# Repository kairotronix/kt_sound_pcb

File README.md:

# kt_sound_pcb

This is the schematic and PCB design files for interfacing with the DE10-Nano development kit for the KT Sound FPGA synthesizer design.

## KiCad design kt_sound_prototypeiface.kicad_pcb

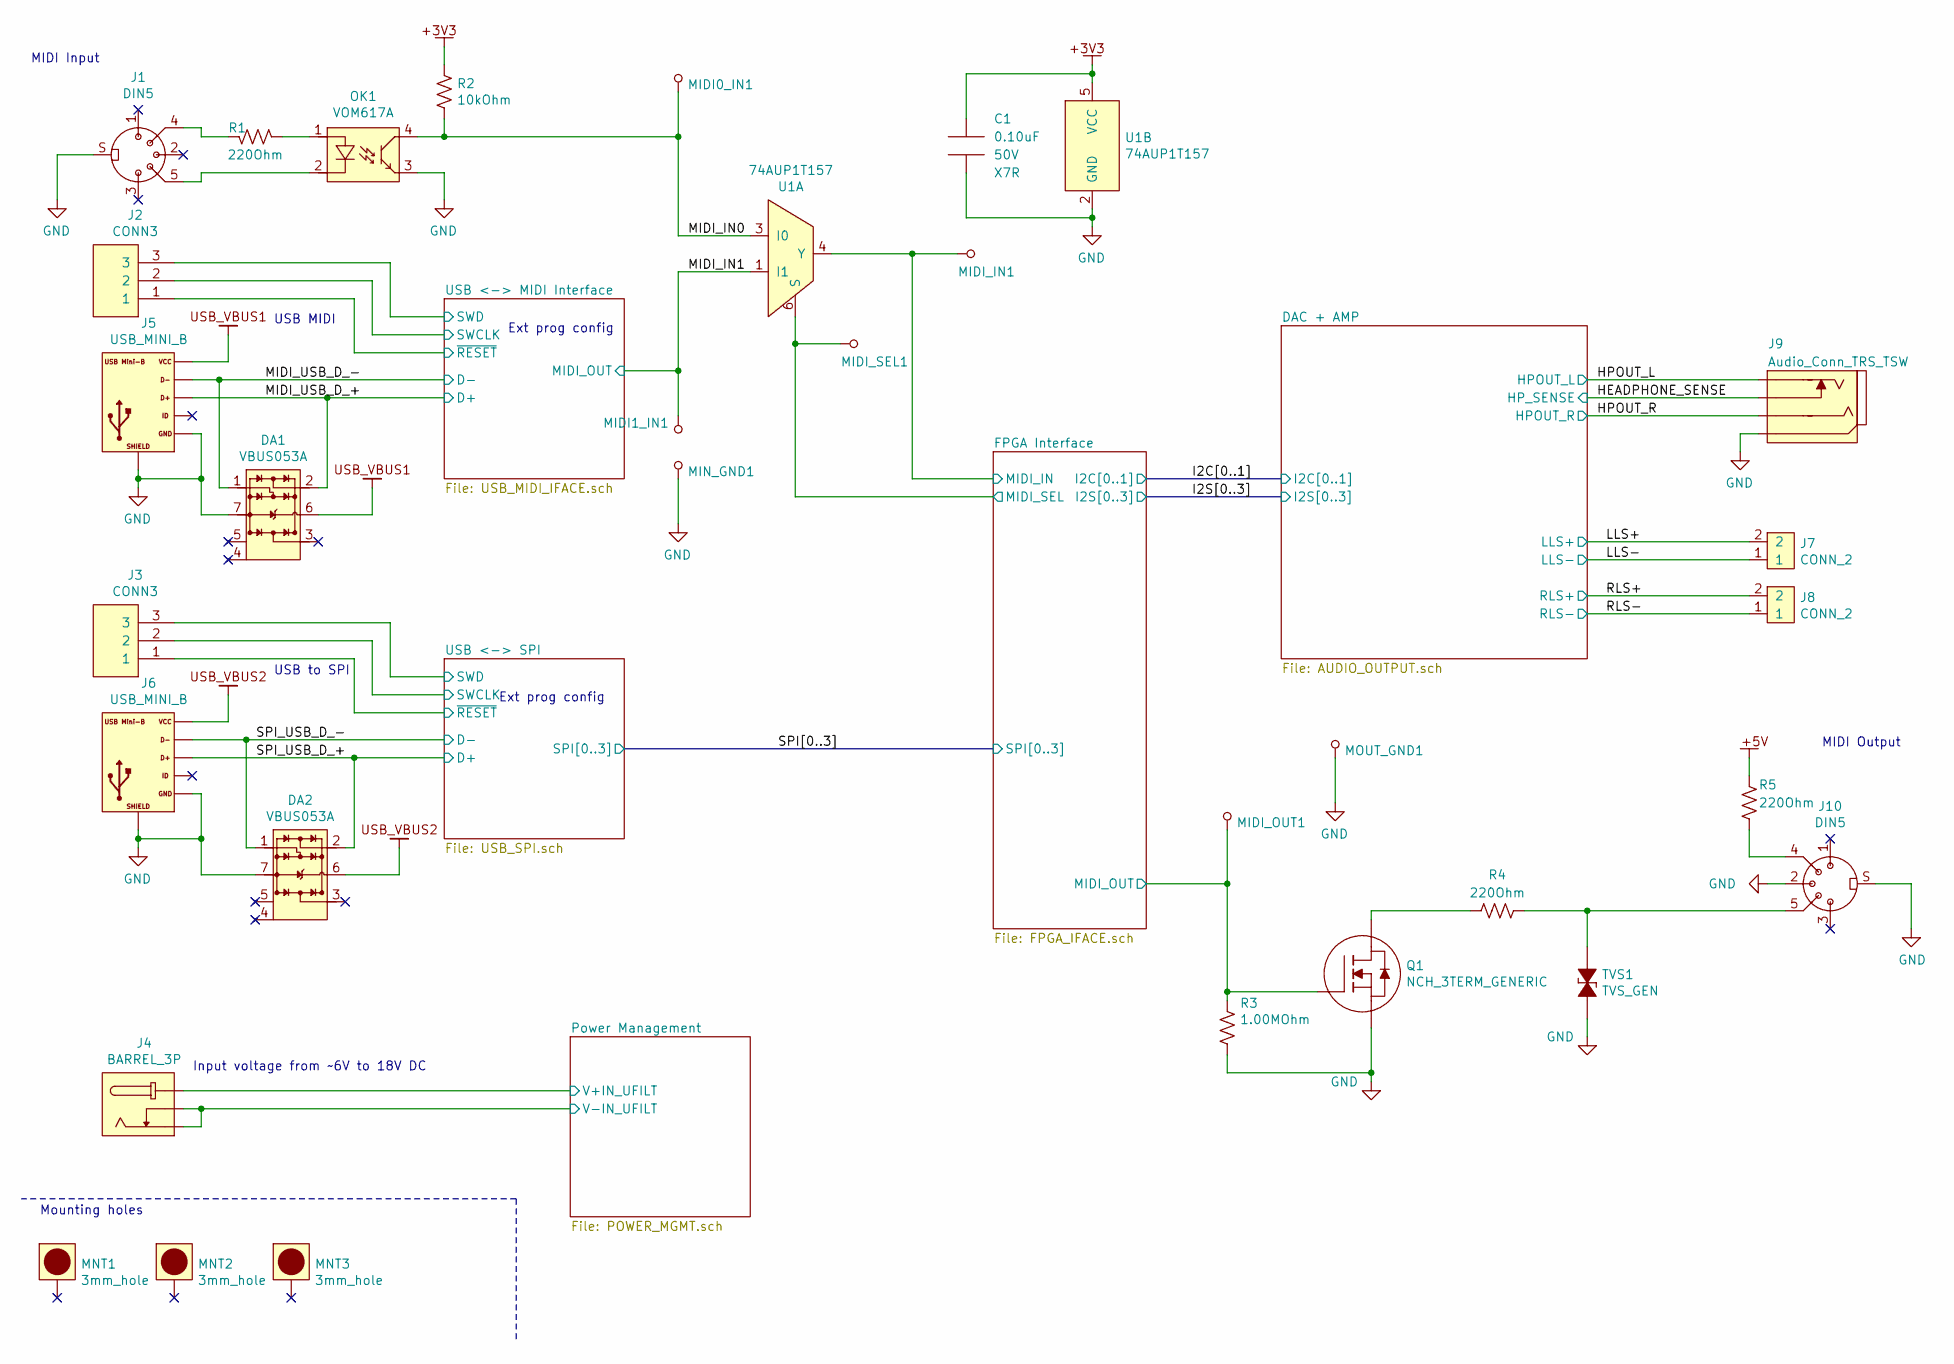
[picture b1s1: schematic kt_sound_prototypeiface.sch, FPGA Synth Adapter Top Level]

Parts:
C1: 0.10uF; CAP_0603; Voltage 50V; Tolerance XX %
DA1, DA2: VBUS053A; UFDFN-6-EP; MFG1 P/N VBUS053A
J1, J10: DIN5; DIN-5-CUI
J2, J3: CONN3; 1x03_0.1inch_vertical_header
J4: BARREL_3P; BarrelJack_CUI_PJ-102B; MFG1 P/N MFG1 P/N
J5, J6: USB_MINI_B; USB_MINIB_THT_TE_2172034-1
J7, J8: CONN_2; 1x02_0.1inch_vertical_header; MFG1 P/N MFG1 P/N
J9: Audio_Conn_TRS_TSW; Jack_3.5mm_CUI_SJ-3524-SMT; MFG1 P/N MFG1 P/N
MIDI0_IN1, MIDI1_IN1: TP_SMALL; TP_1mm; MFG P/N N/A
MIDI_IN1: TP_SMALL; TP_1mm; MFG P/N N/A
MIDI_OUT1: TP_SMALL; TP_1mm; MFG P/N N/A
MIDI_SEL1: TP_SMALL; TP_1mm; MFG P/N N/A
MIN_GND1: TP_SMALL; TP_1mm; MFG P/N N/A
MNT1, MNT2, MNT3: 3mm_hole; mnt_3mm_plated
MOUT_GND1: TP_SMALL; TP_1mm; MFG P/N N/A
OK1: VOM617A; 4-SMD_GW; MFG1 P/N VOM617A
Q1: NCH_3TERM_GENERIC; SOT23
R1: 220Ohm; RES_0603; Tolerance XX %
R2: 10kOhm; RES_0603; Tolerance XX %
R3: 1.00MOhm; RES_0603; Tolerance 10 %
R4, R5: 220Ohm; RES_0603; Tolerance 10 %
TVS1: TVS_GEN; SOD-523; Voltage - Reverse Stand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 X V; Voltage - Breakdown X V; MFG1 P/N MFG1 P/N
U1: 74AUP1T157; TSSOP-6; MFG1 P/N SN74AUP1T157

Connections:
3V3: C1.1, R2.1, U1.5 (VCC); also elsewhere on the board
5V: R5.2; also elsewhere on the board
/FPGA Interface/MIDI_IN: MIDI_IN1.1, U1.4 (Y); also elsewhere on the board
/FPGA Interface/MIDI_OUT: MIDI_OUT1.1, Q1.1 (G), R3.1; also elsewhere on the board
/FPGA Interface/MIDI_SEL: MIDI_SEL1.1, U1.6 (S); also elsewhere on the board
/HEADPHONE_SENSE: J9.10 (TS); also elsewhere on the board
/HPOUT_L: J9.2 (T); also elsewhere on the board
/HPOUT_R: J9.3 (R); also elsewhere on the board
/LLS+: J7.2; also elsewhere on the board
/LLS-: J7.1; also elsewhere on the board
/MIDI_IN0: MIDI0_IN1.1, OK1.4, R2.2, U1.3 (I0)
/MIDI_IN1: MIDI1_IN1.1, U1.1 (I1); also elsewhere on the board
/MIDI_USB_D_+: DA1.2 (I/O), J5.3; also elsewhere on the board
/MIDI_USB_D_-: DA1.1 (I/O), J5.2; also elsewhere on the board
/Power Management/V+IN_UFILT: J4.1 (BARREL); also elsewhere on the board
/RLS+: J8.2; also elsewhere on the board
/RLS-: J8.1; also elsewhere on the board
/SPI_USB_D_+: DA2.2 (I/O), J6.3; also elsewhere on the board
/SPI_USB_D_-: DA2.1 (I/O), J6.2; also elsewhere on the board
/USB <-> MIDI Interface/SWCLK: J2.2; also elsewhere on the board
/USB <-> MIDI Interface/SWD: J2.3; also elsewhere on the board
/USB <-> MIDI Interface/~RESET: J2.1; also elsewhere on the board
/USB <-> SPI/SWCLK: J3.2; also elsewhere on the board
/USB <-> SPI/SWD: J3.3; also elsewhere on the board
/USB <-> SPI/~RESET: J3.1; also elsewhere on the board
GND: C1.2, DA1.7 (GND), DA2.7 (GND), J1.S, J4.2 (SHIELD), J4.3 (CONTACT), J5.5, J5.SHIELD, J6.5, J6.SHIELD, J9.1 (S), J10.2, J10.S, MIN_GND1.1, MOUT_GND1.1, OK1.3, Q1.2 (S), R3.2, TVS1.2, U1.2 (GND); also elsewhere on the board
unnamed: J1.4, R1.1
unnamed: J1.5, OK1.2
unnamed: J10.4, R5.1
unnamed: J10.5, R4.1, TVS1.1
unnamed: OK1.1, R1.2
unnamed: Q1.3 (D), R4.2
USB_VBUS1: DA1.6 (V-), J5.1; also elsewhere on the board
USB_VBUS2: DA2.6 (V-), J6.1; also elsewhere on the board

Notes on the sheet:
USB to SPI
USB MIDI
MIDI Output
MIDI Input
Ext prog config
Input voltage from ~~6V to 18V DC
Mounting holes

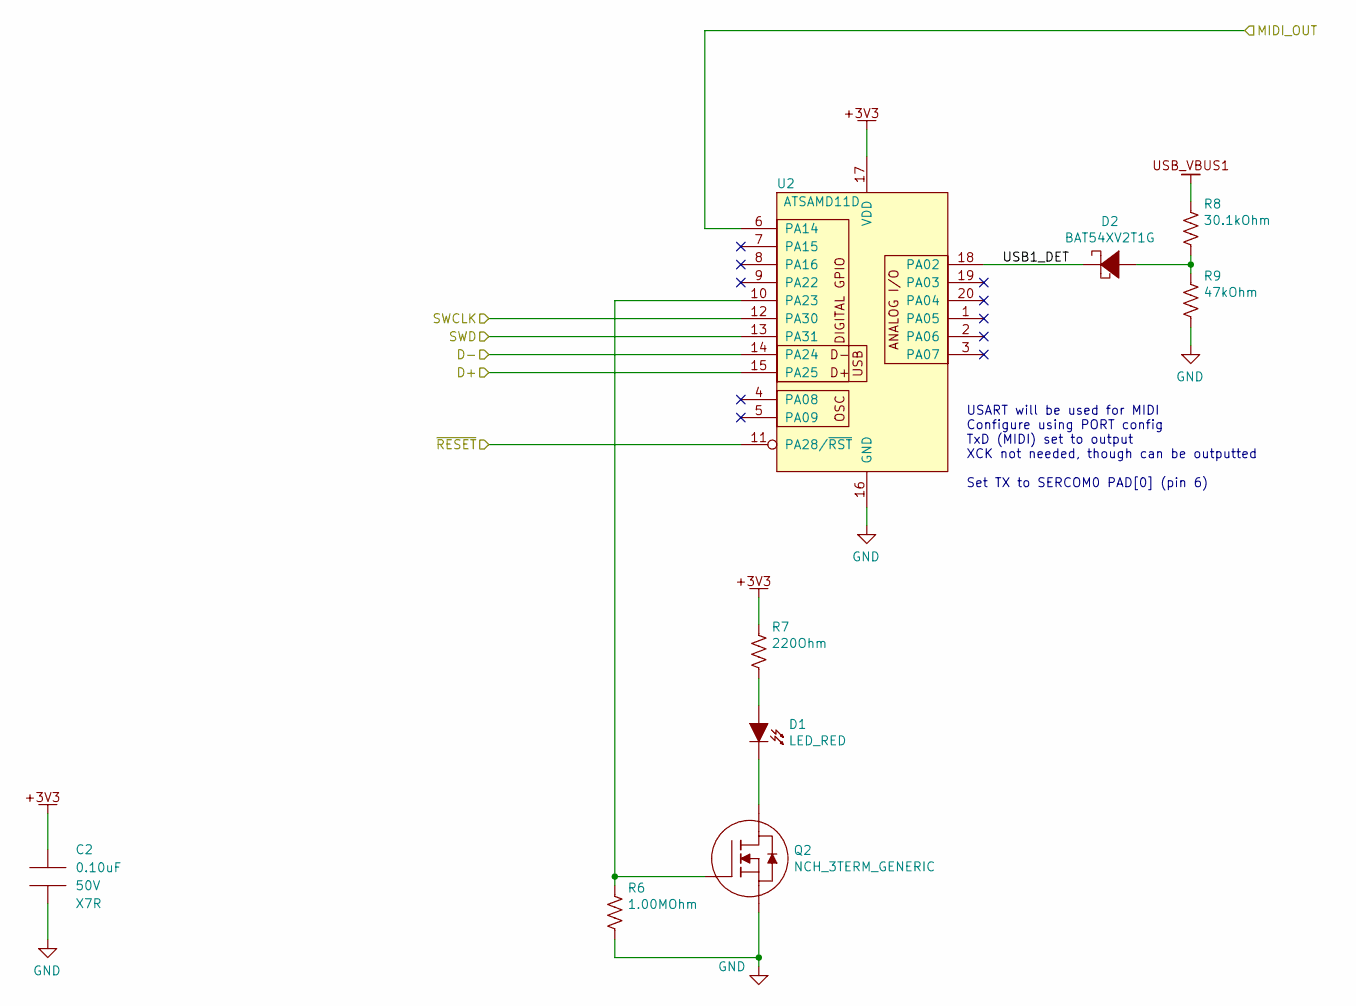
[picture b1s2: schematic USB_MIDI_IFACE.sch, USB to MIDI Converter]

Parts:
C2: 0.10uF; CAP_0603; Voltage 50V; Tolerance XX %
D1: LED_RED; LED_0805
D2: BAT54XV2T1G; SOD-523
Q2: NCH_3TERM_GENERIC; SOT23
R6: 1.00MOhm; RES_0603; Tolerance 10 %
R7: 220Ohm; RES_0603; Tolerance XX %
R8: 30.1kOhm; RES_0603; Tolerance XX %
R9: 47kOhm; RES_0603; Tolerance XX %
U2: ATSAMD11D; SOIC-20; MFG1 P/N ATSAMD11D14A-SSUT

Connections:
3V3: C2.1, R7.1, U2.17 (VDD); also elsewhere on the board
/MIDI_IN1: U2.6 (PA14); also elsewhere on the board
/MIDI_USB_D_+: U2.15 (PA25); also elsewhere on the board
/MIDI_USB_D_-: U2.14 (PA24); also elsewhere on the board
/USB <-> MIDI Interface/SWCLK: U2.12 (PA30); also elsewhere on the board
/USB <-> MIDI Interface/SWD: U2.13 (PA31); also elsewhere on the board
/USB <-> MIDI Interface/USB1_DET: D2.2, U2.18 (PA02)
/USB <-> MIDI Interface/~RESET: U2.11 (PA28/~RST); also elsewhere on the board
GND: C2.2, Q2.2 (S), R6.2, R9.2, U2.16 (GND); also elsewhere on the board
unnamed: D1.1, R7.2
unnamed: D1.2, Q2.3 (D)
unnamed: D2.1, R8.2, R9.1
unnamed: Q2.1 (G), R6.1, U2.10 (PA23)
USB_VBUS1: R8.1; also elsewhere on the board

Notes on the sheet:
USART will be used for MIDI Configure using PORT config TxD (MIDI) set to output XCK not needed, though can be outputted Set TX to SERCOM0 PAD[0] (pin 6)

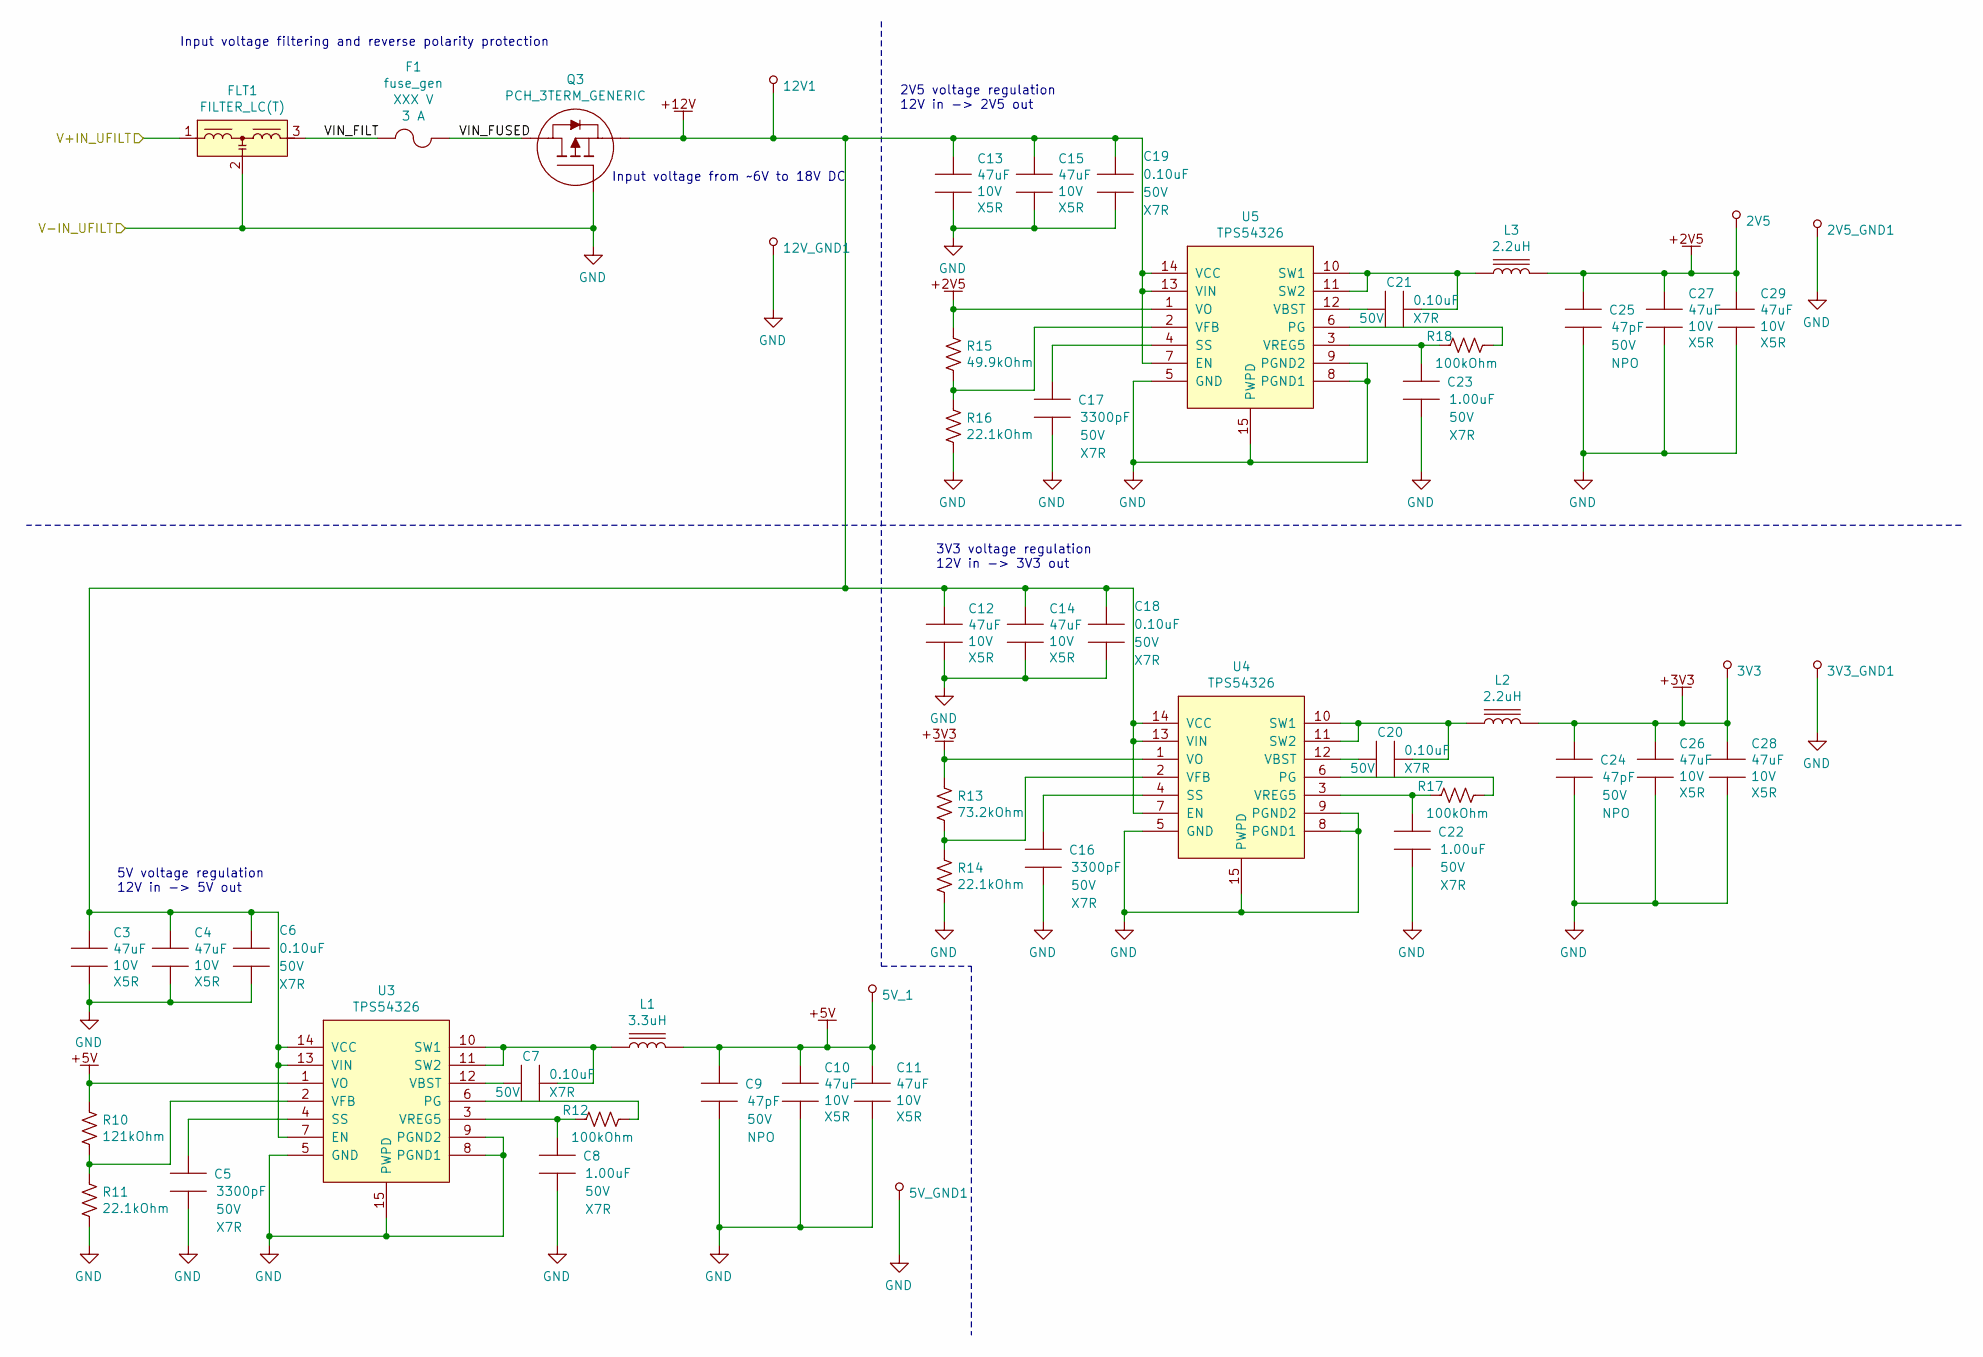
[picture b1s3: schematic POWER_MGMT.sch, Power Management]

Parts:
2V5, 2V5_GND1, 3V3, 3V3_GND1, 5V_1, 5V_GND1, 12V1, 12V_GND1: TP_SMALL; TP_1mm; MFG P/N N/A
C3, C4, C10, C11, C12, C13, C14, C15, C26, C27, C28, C29: 47uF; CAP_0805; Voltage 10V; Tolerance XX %
C5, C16, C17: 3300pF; CAP_0603; Voltage 50V; Tolerance XX %
C6, C7, C18, C19, C20, C21: 0.10uF; CAP_0603; Voltage 50V; Tolerance XX %
C8, C22, C23: 1.00uF; CAP_0603; Voltage 50V; Tolerance XX %
C9, C24, C25: 47pF; CAP_0603; Voltage 50V; Tolerance XX %
F1: fuse_gen; RES_0603; Voltage XXX V; MFG1 P/N MFG1 P/N
FLT1: FILTER_LC(T); FIL_NFE31PT222Z1E9L
L1: 3.3uH; L_Radial_THT_5mm; Voltage X V; MFG1 P/N MFG1 P/N
L2, L3: 2.2uH; L_Radial_THT_5mm; Voltage X V; MFG1 P/N MFG1 P/N
Q3: PCH_3TERM_GENERIC; SOT23
R10: 121kOhm; RES_0603; Tolerance XX %
R11, R14, R16: 22.1kOhm; RES_0603; Tolerance XX %
R12, R17, R18: 100kOhm; RES_0603; Tolerance XX %
R13: 73.2kOhm; RES_0603; Tolerance XX %
R15: 49.9kOhm; RES_0603; Tolerance XX %
U3, U4, U5: TPS54326; HTSSOP-14-EP; MFG1 P/N TPS54326

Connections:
2V5: 2V5.1, C25.1, C27.1, C29.1, L3.2, R15.1, U5.1 (VO); also elsewhere on the board
3V3: 3V3.1, C24.1, C26.1, C28.1, L2.2, R13.1, U4.1 (VO); also elsewhere on the board
5V: 5V_1.1, C9.1, C10.1, C11.1, L1.2, R10.1, U3.1 (VO); also elsewhere on the board
12V: 12V1.1, C3.1, C4.1, C6.1, C12.1, C13.1, C14.1, C15.1, C18.1, C19.1, Q3.2 (S), U3.7 (EN), U3.13 (VIN), U3.14 (VCC), U4.7 (EN), U4.13 (VIN), U4.14 (VCC), U5.7 (EN), U5.13 (VIN), U5.14 (VCC)
/Power Management/V+IN_UFILT: FLT1.1 (Input); also elsewhere on the board
/Power Management/VIN_FILT: F1.1, FLT1.3 (Output)
/Power Management/VIN_FUSED: F1.2, Q3.3 (D)
GND: 2V5_GND1.1, 3V3_GND1.1, 5V_GND1.1, 12V_GND1.1, C3.2, C4.2, C5.2, C6.2, C8.2, C9.2, C10.2, C11.2, C12.2, C13.2, C14.2, C15.2, C16.2, C17.2, C18.2, C19.2, C22.2, C23.2, C24.2, C25.2, C26.2, C27.2, C28.2, C29.2, FLT1.2 (GND), Q3.1 (G), R11.2, R14.2, R16.2, U3.5 (GND), U3.8 (PGND1), U3.9 (PGND2), U3.15 (PWPD), U4.5 (GND), U4.8 (PGND1), U4.9 (PGND2), U4.15 (PWPD), U5.5 (GND), U5.8 (PGND1), U5.9 (PGND2), U5.15 (PWPD); also elsewhere on the board
unnamed: C5.1, U3.4 (SS)
unnamed: C7.1, U3.12 (VBST)
unnamed: C7.2, L1.1, U3.10 (SW1), U3.11 (SW2)
unnamed: C8.1, R12.1, U3.3 (VREG5)
unnamed: C16.1, U4.4 (SS)
unnamed: C17.1, U5.4 (SS)
unnamed: C20.1, U4.12 (VBST)
unnamed: C20.2, L2.1, U4.10 (SW1), U4.11 (SW2)
unnamed: C21.1, U5.12 (VBST)
unnamed: C21.2, L3.1, U5.10 (SW1), U5.11 (SW2)
unnamed: C22.1, R17.1, U4.3 (VREG5)
unnamed: C23.1, R18.1, U5.3 (VREG5)
unnamed: R10.2, R11.1, U3.2 (VFB)
unnamed: R12.2, U3.6 (PG)
unnamed: R13.2, R14.1, U4.2 (VFB)
unnamed: R15.2, R16.1, U5.2 (VFB)
unnamed: R17.2, U4.6 (PG)
unnamed: R18.2, U5.6 (PG)

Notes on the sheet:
2V5 voltage regulation 12V in -> 2V5 out
3V3 voltage regulation 12V in -> 3V3 out
5V voltage regulation 12V in -> 5V out
Input voltage filtering and reverse polarity protection
Input voltage from ~~6V to 18V DC

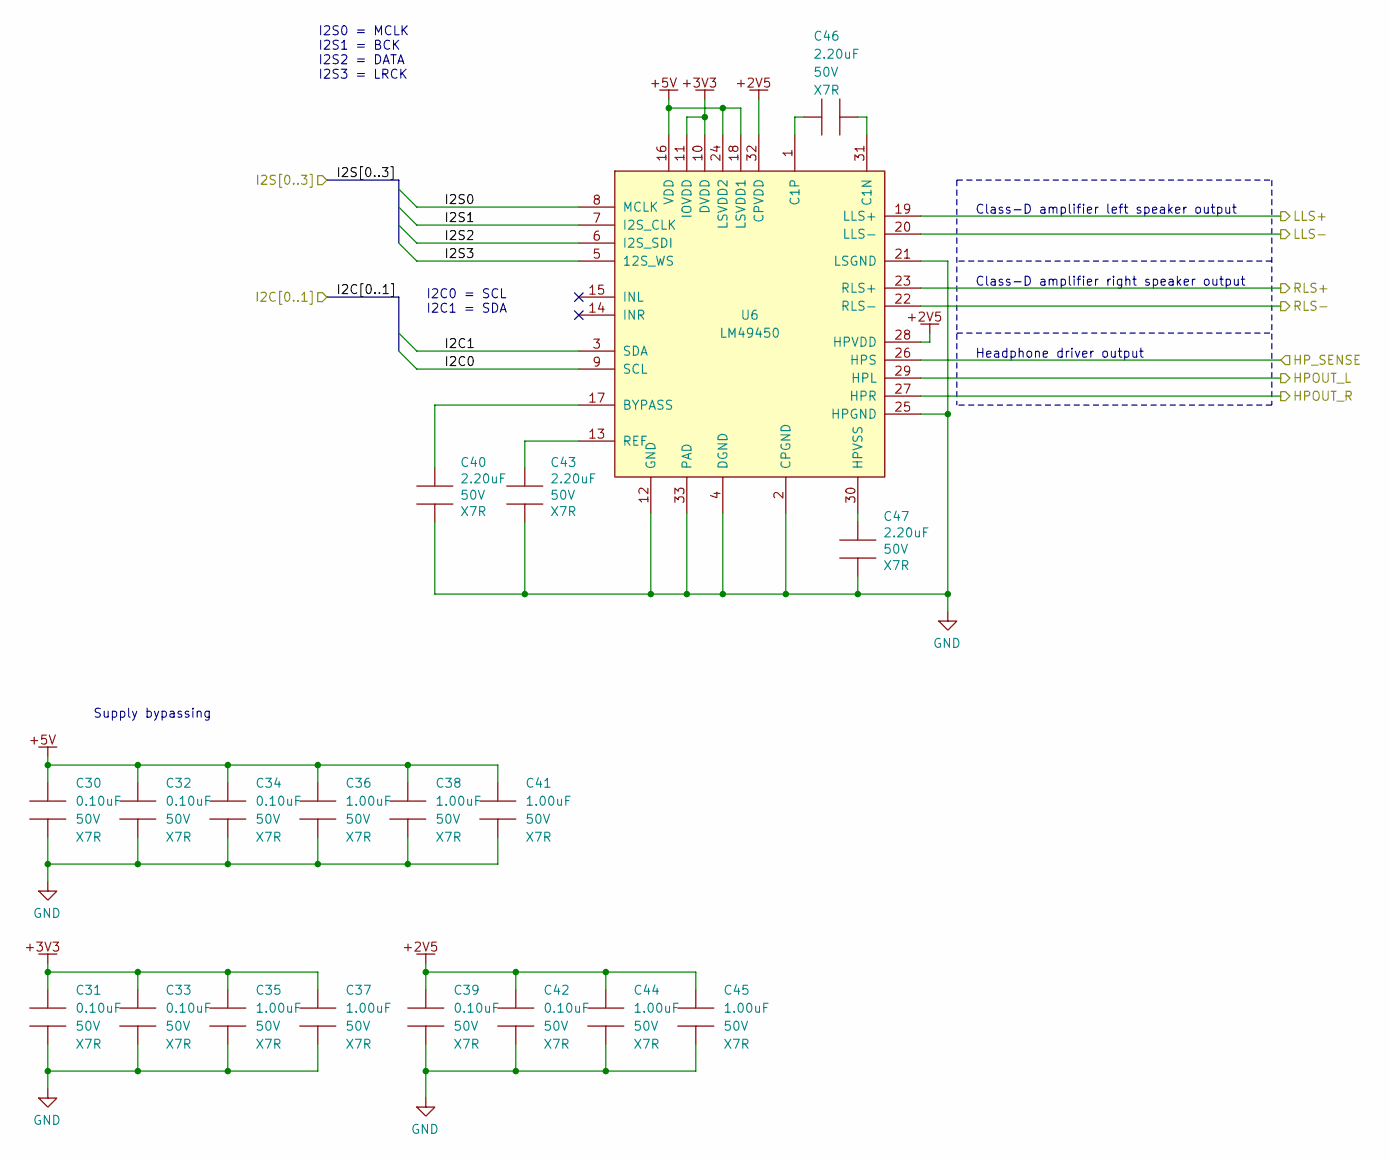
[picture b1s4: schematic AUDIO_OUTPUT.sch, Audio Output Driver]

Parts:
C30, C31, C32, C33, C34, C39, C42: 0.10uF; CAP_0603; Voltage 50V; Tolerance XX %
C35, C36, C37, C38, C41, C44, C45: 1.00uF; CAP_0603; Voltage 50V; Tolerance XX %
C40, C43, C46, C47: 2.20uF; CAP_0603; Voltage 50V; Tolerance XX %
U6: LM49450; WQFN-32; MFG1 P/N LM49450

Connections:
2V5: C39.1, C42.1, C44.1, C45.1, U6.28 (HPVDD), U6.32 (CPVDD); also elsewhere on the board
3V3: C31.1, C33.1, C35.1, C37.1, U6.10 (DVDD), U6.11 (IOVDD); also elsewhere on the board
5V: C30.1, C32.1, C34.1, C36.1, C38.1, C41.1, U6.16 (VDD), U6.18 (LSVDD1), U6.24 (LSVDD2); also elsewhere on the board
/DAC + AMP/I2C0: U6.9 (SCL); also elsewhere on the board
/DAC + AMP/I2C1: U6.3 (SDA); also elsewhere on the board
/DAC + AMP/I2S0: U6.8 (MCLK); also elsewhere on the board
/DAC + AMP/I2S1: U6.7 (I2S_CLK); also elsewhere on the board
/DAC + AMP/I2S2: U6.6 (I2S_SDI); also elsewhere on the board
/DAC + AMP/I2S3: U6.5 (12S_WS); also elsewhere on the board
/HEADPHONE_SENSE: U6.26 (HPS); also elsewhere on the board
/HPOUT_L: U6.29 (HPL); also elsewhere on the board
/HPOUT_R: U6.27 (HPR); also elsewhere on the board
/LLS+: U6.19 (LLS+); also elsewhere on the board
/LLS-: U6.20 (LLS-); also elsewhere on the board
/RLS+: U6.23 (RLS+); also elsewhere on the board
/RLS-: U6.22 (RLS-); also elsewhere on the board
GND: C30.2, C31.2, C32.2, C33.2, C34.2, C35.2, C36.2, C37.2, C38.2, C39.2, C40.2, C41.2, C42.2, C43.2, C44.2, C45.2, C47.2, U6.2 (CPGND), U6.4 (DGND), U6.12 (GND), U6.21 (LSGND), U6.25 (HPGND), U6.33 (PAD); also elsewhere on the board
unnamed: C40.1, U6.17 (BYPASS)
unnamed: C43.1, U6.13 (REF)
unnamed: C46.1, U6.1 (C1P)
unnamed: C46.2, U6.31 (C1N)
unnamed: C47.1, U6.30 (HPVSS)

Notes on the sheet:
Class-D amplifier left speaker output
Class-D amplifier right speaker output
Headphone driver output
Supply bypassing
I2S0 = MCLK I2S1 = BCK I2S2 = DATA I2S3 = LRCK
I2C0 = SCL I2C1 = SDA

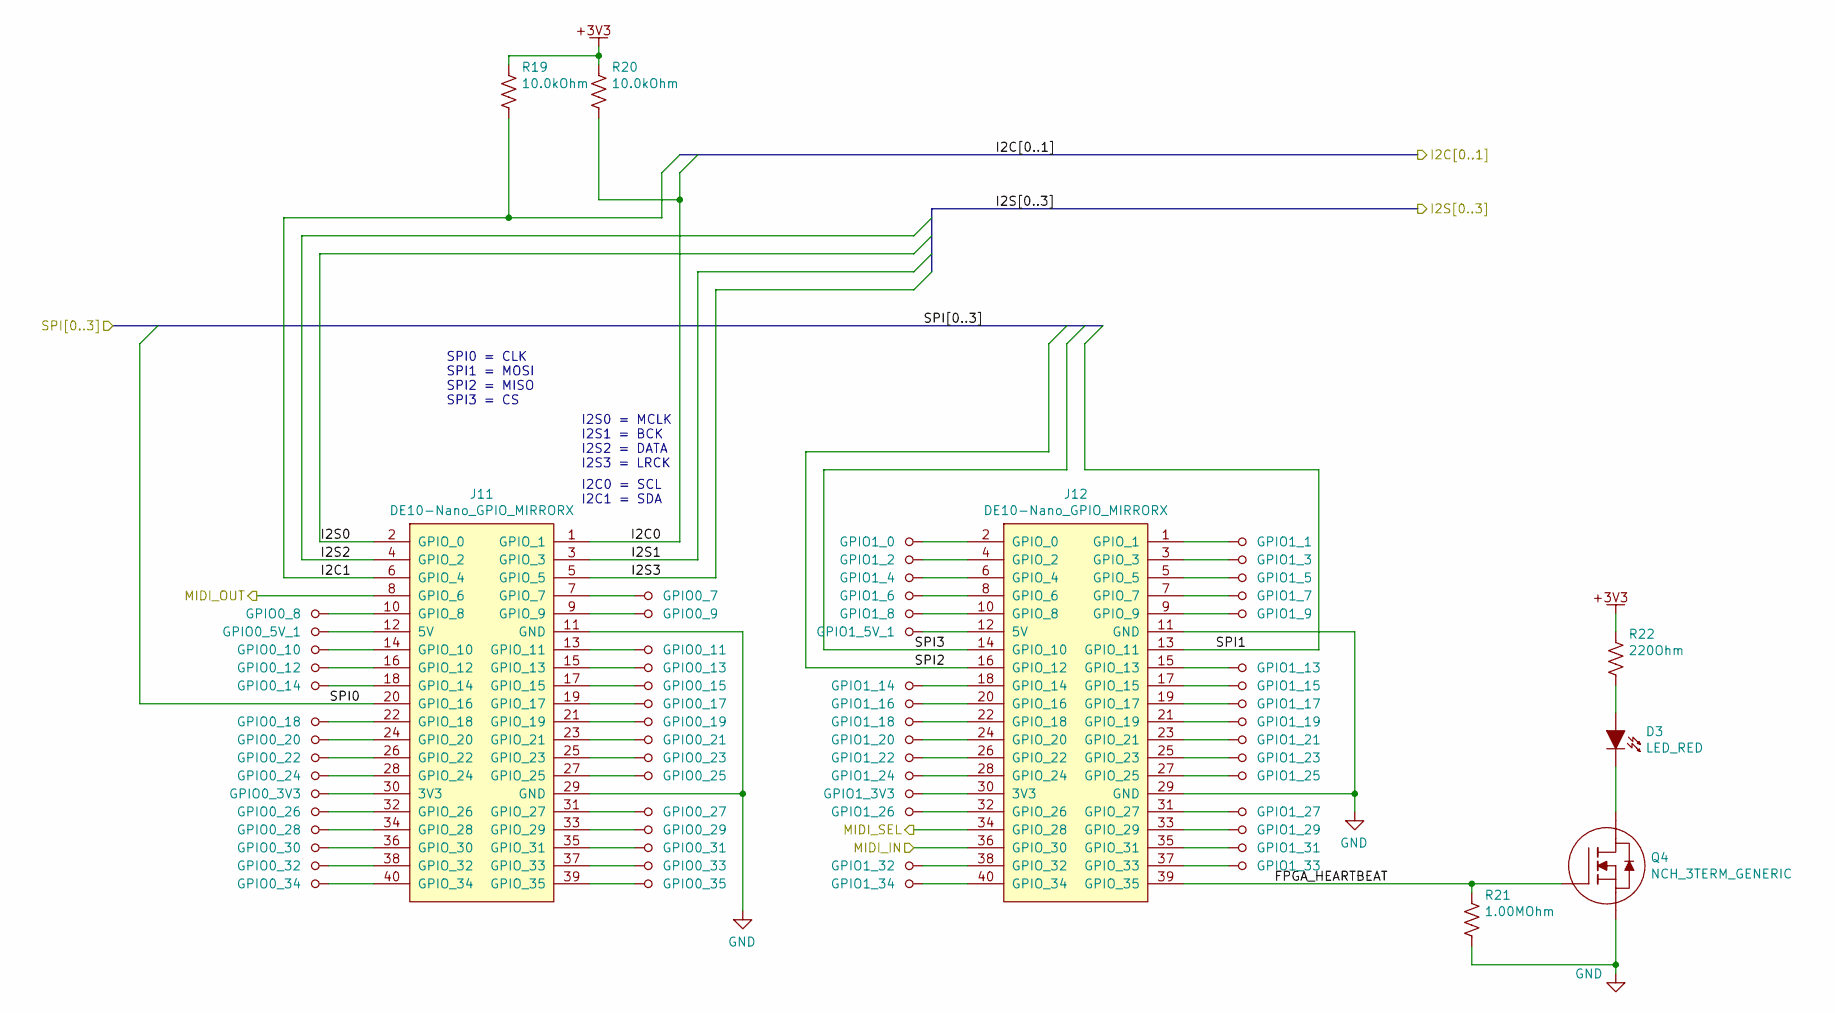
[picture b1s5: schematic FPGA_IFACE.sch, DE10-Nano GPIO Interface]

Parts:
D3: LED_RED; LED_0805
GPIO0_3V3, GPIO0_5V_1, GPIO0_7, GPIO0_8, GPIO0_9, GPIO0_10, GPIO0_11, GPIO0_12, GPIO0_13, GPIO0_14, GPIO0_15, GPIO0_17, GPIO0_18, GPIO0_19, GPIO0_20, GPIO0_21, GPIO0_22, GPIO0_23, GPIO0_24, GPIO0_25, GPIO0_26, GPIO0_27, GPIO0_28, GPIO0_29, GPIO0_30, GPIO0_31, GPIO0_32, GPIO0_33, GPIO0_34, GPIO0_35, GPIO1_0, GPIO1_1, GPIO1_2, GPIO1_3, GPIO1_3V3, GPIO1_4, GPIO1_5, GPIO1_5V_1, GPIO1_6, GPIO1_7, GPIO1_8, GPIO1_9, GPIO1_13, GPIO1_14, GPIO1_15, GPIO1_16, GPIO1_17, GPIO1_18, GPIO1_19, GPIO1_20, GPIO1_21, GPIO1_22, GPIO1_23, GPIO1_24, GPIO1_25, GPIO1_26, GPIO1_27, GPIO1_29, GPIO1_31, GPIO1_32, GPIO1_33, GPIO1_34: TP_SMALL; TP_1mm; MFG P/N N/A
J11, J12: DE10-Nano_GPIO_MIRRORX; DE10_GPIO_HEADER
Q4: NCH_3TERM_GENERIC; SOT23
R19, R20: 10.0kOhm; RES_0603; Tolerance XX %
R21: 1.00MOhm; RES_0603; Tolerance 10 %
R22: 220Ohm; RES_0603; Tolerance XX %

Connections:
3V3: R19.1, R20.1, R22.1; also elsewhere on the board
/DAC + AMP/I2C0: J11.1 (GPIO_1), R20.2; also elsewhere on the board
/DAC + AMP/I2C1: J11.6 (GPIO_4), R19.2; also elsewhere on the board
/DAC + AMP/I2S0: J11.2 (GPIO_0); also elsewhere on the board
/DAC + AMP/I2S1: J11.3 (GPIO_3); also elsewhere on the board
/DAC + AMP/I2S2: J11.4 (GPIO_2); also elsewhere on the board
/DAC + AMP/I2S3: J11.5 (GPIO_5); also elsewhere on the board
/FPGA Interface/FPGA_HEARTBEAT: J12.39 (GPIO_35), Q4.1 (G), R21.1
/FPGA Interface/MIDI_IN: J12.36 (GPIO_30); also elsewhere on the board
/FPGA Interface/MIDI_OUT: J11.8 (GPIO_6); also elsewhere on the board
/FPGA Interface/MIDI_SEL: J12.34 (GPIO_28); also elsewhere on the board
/FPGA Interface/SPI0: J11.20 (GPIO_16); also elsewhere on the board
/FPGA Interface/SPI1: J12.13 (GPIO_11); also elsewhere on the board
/FPGA Interface/SPI2: J12.16 (GPIO_12); also elsewhere on the board
/FPGA Interface/SPI3: J12.14 (GPIO_10); also elsewhere on the board
GND: J11.11 (GND), J11.29 (GND), J12.11 (GND), J12.29 (GND), Q4.2 (S), R21.2; also elsewhere on the board
unnamed: D3.1, R22.2
unnamed: D3.2, Q4.3 (D)
unnamed: GPIO0_3V3.1, J11.30 (3V3)
unnamed: GPIO0_5V_1.1, J11.12 (5V)
unnamed: GPIO0_7.1, J11.7 (GPIO_7)
unnamed: GPIO0_8.1, J11.10 (GPIO_8)
unnamed: GPIO0_9.1, J11.9 (GPIO_9)
unnamed: GPIO0_10.1, J11.14 (GPIO_10)
unnamed: GPIO0_11.1, J11.13 (GPIO_11)
unnamed: GPIO0_12.1, J11.16 (GPIO_12)
unnamed: GPIO0_13.1, J11.15 (GPIO_13)
unnamed: GPIO0_14.1, J11.18 (GPIO_14)
unnamed: GPIO0_15.1, J11.17 (GPIO_15)
unnamed: GPIO0_17.1, J11.19 (GPIO_17)
unnamed: GPIO0_18.1, J11.22 (GPIO_18)
unnamed: GPIO0_19.1, J11.21 (GPIO_19)
unnamed: GPIO0_20.1, J11.24 (GPIO_20)
unnamed: GPIO0_21.1, J11.23 (GPIO_21)
unnamed: GPIO0_22.1, J11.26 (GPIO_22)
unnamed: GPIO0_23.1, J11.25 (GPIO_23)
unnamed: GPIO0_24.1, J11.28 (GPIO_24)
unnamed: GPIO0_25.1, J11.27 (GPIO_25)
unnamed: GPIO0_26.1, J11.32 (GPIO_26)
unnamed: GPIO0_27.1, J11.31 (GPIO_27)
unnamed: GPIO0_28.1, J11.34 (GPIO_28)
unnamed: GPIO0_29.1, J11.33 (GPIO_29)
unnamed: GPIO0_30.1, J11.36 (GPIO_30)
unnamed: GPIO0_31.1, J11.35 (GPIO_31)
unnamed: GPIO0_32.1, J11.38 (GPIO_32)
unnamed: GPIO0_33.1, J11.37 (GPIO_33)
unnamed: GPIO0_34.1, J11.40 (GPIO_34)
unnamed: GPIO0_35.1, J11.39 (GPIO_35)
unnamed: GPIO1_0.1, J12.2 (GPIO_0)
unnamed: GPIO1_1.1, J12.1 (GPIO_1)
unnamed: GPIO1_2.1, J12.4 (GPIO_2)
unnamed: GPIO1_3.1, J12.3 (GPIO_3)
unnamed: GPIO1_3V3.1, J12.30 (3V3)
unnamed: GPIO1_4.1, J12.6 (GPIO_4)
unnamed: GPIO1_5.1, J12.5 (GPIO_5)
unnamed: GPIO1_5V_1.1, J12.12 (5V)
unnamed: GPIO1_6.1, J12.8 (GPIO_6)
unnamed: GPIO1_7.1, J12.7 (GPIO_7)
unnamed: GPIO1_8.1, J12.10 (GPIO_8)
unnamed: GPIO1_9.1, J12.9 (GPIO_9)
unnamed: GPIO1_13.1, J12.15 (GPIO_13)
unnamed: GPIO1_14.1, J12.18 (GPIO_14)
unnamed: GPIO1_15.1, J12.17 (GPIO_15)
unnamed: GPIO1_16.1, J12.20 (GPIO_16)
unnamed: GPIO1_17.1, J12.19 (GPIO_17)
unnamed: GPIO1_18.1, J12.22 (GPIO_18)
unnamed: GPIO1_19.1, J12.21 (GPIO_19)
unnamed: GPIO1_20.1, J12.24 (GPIO_20)
unnamed: GPIO1_21.1, J12.23 (GPIO_21)
unnamed: GPIO1_22.1, J12.26 (GPIO_22)
unnamed: GPIO1_23.1, J12.25 (GPIO_23)
unnamed: GPIO1_24.1, J12.28 (GPIO_24)
unnamed: GPIO1_25.1, J12.27 (GPIO_25)
unnamed: GPIO1_26.1, J12.32 (GPIO_26)
unnamed: GPIO1_27.1, J12.31 (GPIO_27)
unnamed: GPIO1_29.1, J12.33 (GPIO_29)
unnamed: GPIO1_31.1, J12.35 (GPIO_31)
unnamed: GPIO1_32.1, J12.38 (GPIO_32)
unnamed: GPIO1_33.1, J12.37 (GPIO_33)
unnamed: GPIO1_34.1, J12.40 (GPIO_34)

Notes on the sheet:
I2S0 = MCLK I2S1 = BCK I2S2 = DATA I2S3 = LRCK
I2C0 = SCL I2C1 = SDA
SPI0 = CLK SPI1 = MOSI SPI2 = MISO SPI3 = CS

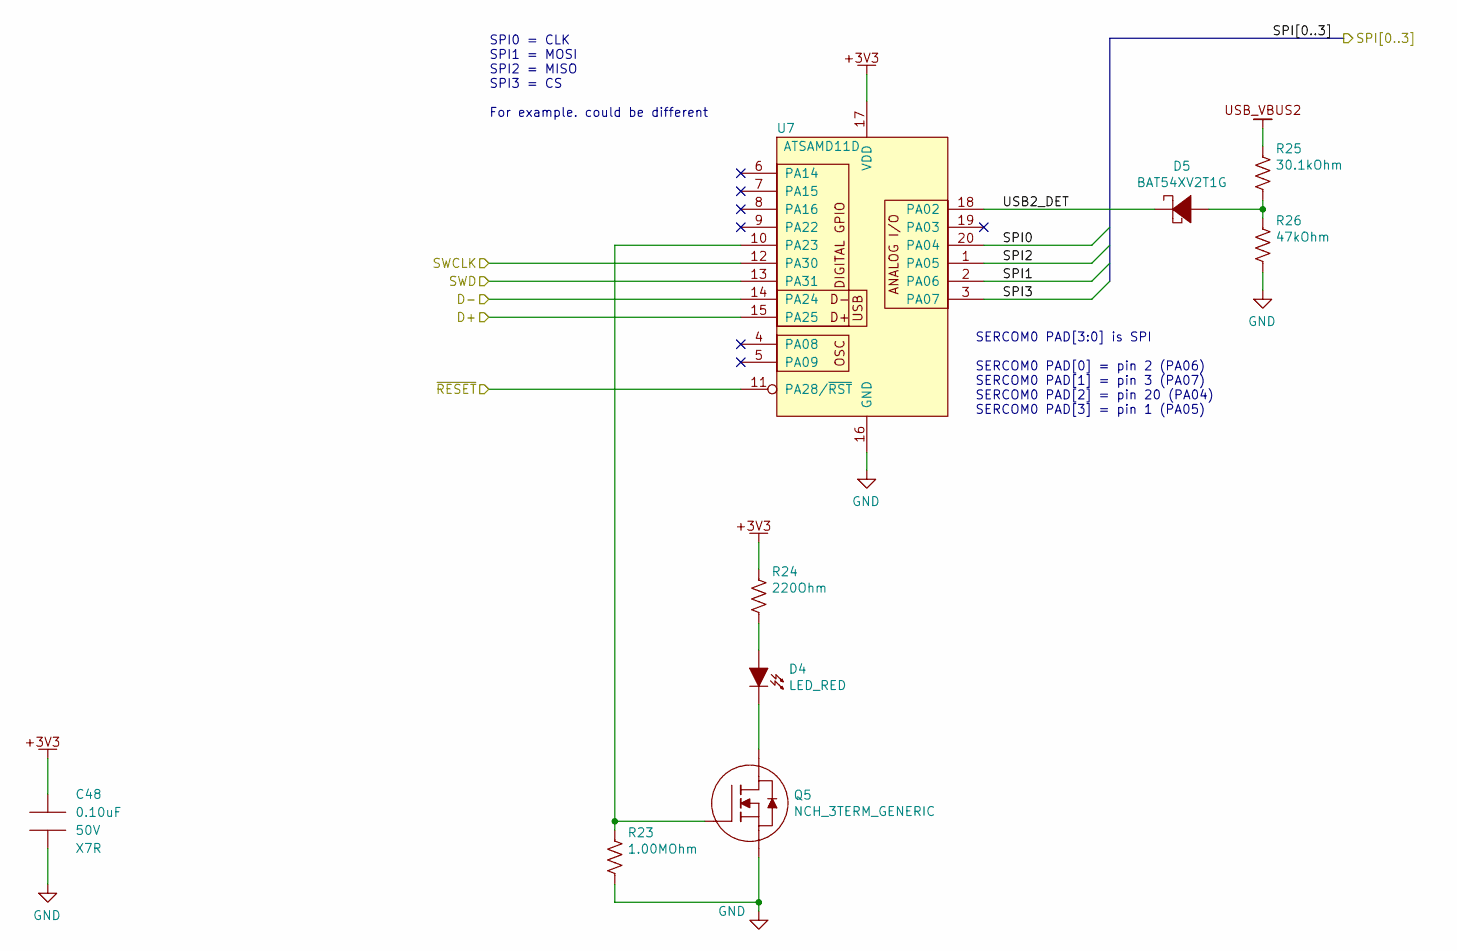
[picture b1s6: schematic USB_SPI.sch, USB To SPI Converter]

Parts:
C48: 0.10uF; CAP_0603; Voltage 50V; Tolerance XX %
D4: LED_RED; LED_0805
D5: BAT54XV2T1G; SOD-523
Q5: NCH_3TERM_GENERIC; SOT23
R23: 1.00MOhm; RES_0603; Tolerance 10 %
R24: 220Ohm; RES_0603; Tolerance XX %
R25: 30.1kOhm; RES_0603; Tolerance XX %
R26: 47kOhm; RES_0603; Tolerance XX %
U7: ATSAMD11D; SOIC-20; MFG1 P/N ATSAMD11D14A-SSUT

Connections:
3V3: C48.1, R24.1, U7.17 (VDD); also elsewhere on the board
/FPGA Interface/SPI0: U7.20 (PA04); also elsewhere on the board
/FPGA Interface/SPI1: U7.2 (PA06); also elsewhere on the board
/FPGA Interface/SPI2: U7.1 (PA05); also elsewhere on the board
/FPGA Interface/SPI3: U7.3 (PA07); also elsewhere on the board
/SPI_USB_D_+: U7.15 (PA25); also elsewhere on the board
/SPI_USB_D_-: U7.14 (PA24); also elsewhere on the board
/USB <-> SPI/SWCLK: U7.12 (PA30); also elsewhere on the board
/USB <-> SPI/SWD: U7.13 (PA31); also elsewhere on the board
/USB <-> SPI/USB2_DET: D5.2, U7.18 (PA02)
/USB <-> SPI/~RESET: U7.11 (PA28/~RST); also elsewhere on the board
GND: C48.2, Q5.2 (S), R23.2, R26.2, U7.16 (GND); also elsewhere on the board
unnamed: D4.1, R24.2
unnamed: D4.2, Q5.3 (D)
unnamed: D5.1, R25.2, R26.1
unnamed: Q5.1 (G), R23.1, U7.10 (PA23)
USB_VBUS2: R25.1; also elsewhere on the board

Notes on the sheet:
SPI0 = CLK SPI1 = MOSI SPI2 = MISO SPI3 = CS For example. could be different
SERCOM0 PAD[3:0] is SPI SERCOM0 PAD[0] = pin 2 (PA06) SERCOM0 PAD[1] = pin 3 (PA07) SERCOM0 PAD[2] = pin 20 (PA04) SERCOM0 PAD[3] = pin 1 (PA05)

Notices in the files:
parts and their libraries:
Copyright 2016 Accelerated Designs. All rights reserved.
